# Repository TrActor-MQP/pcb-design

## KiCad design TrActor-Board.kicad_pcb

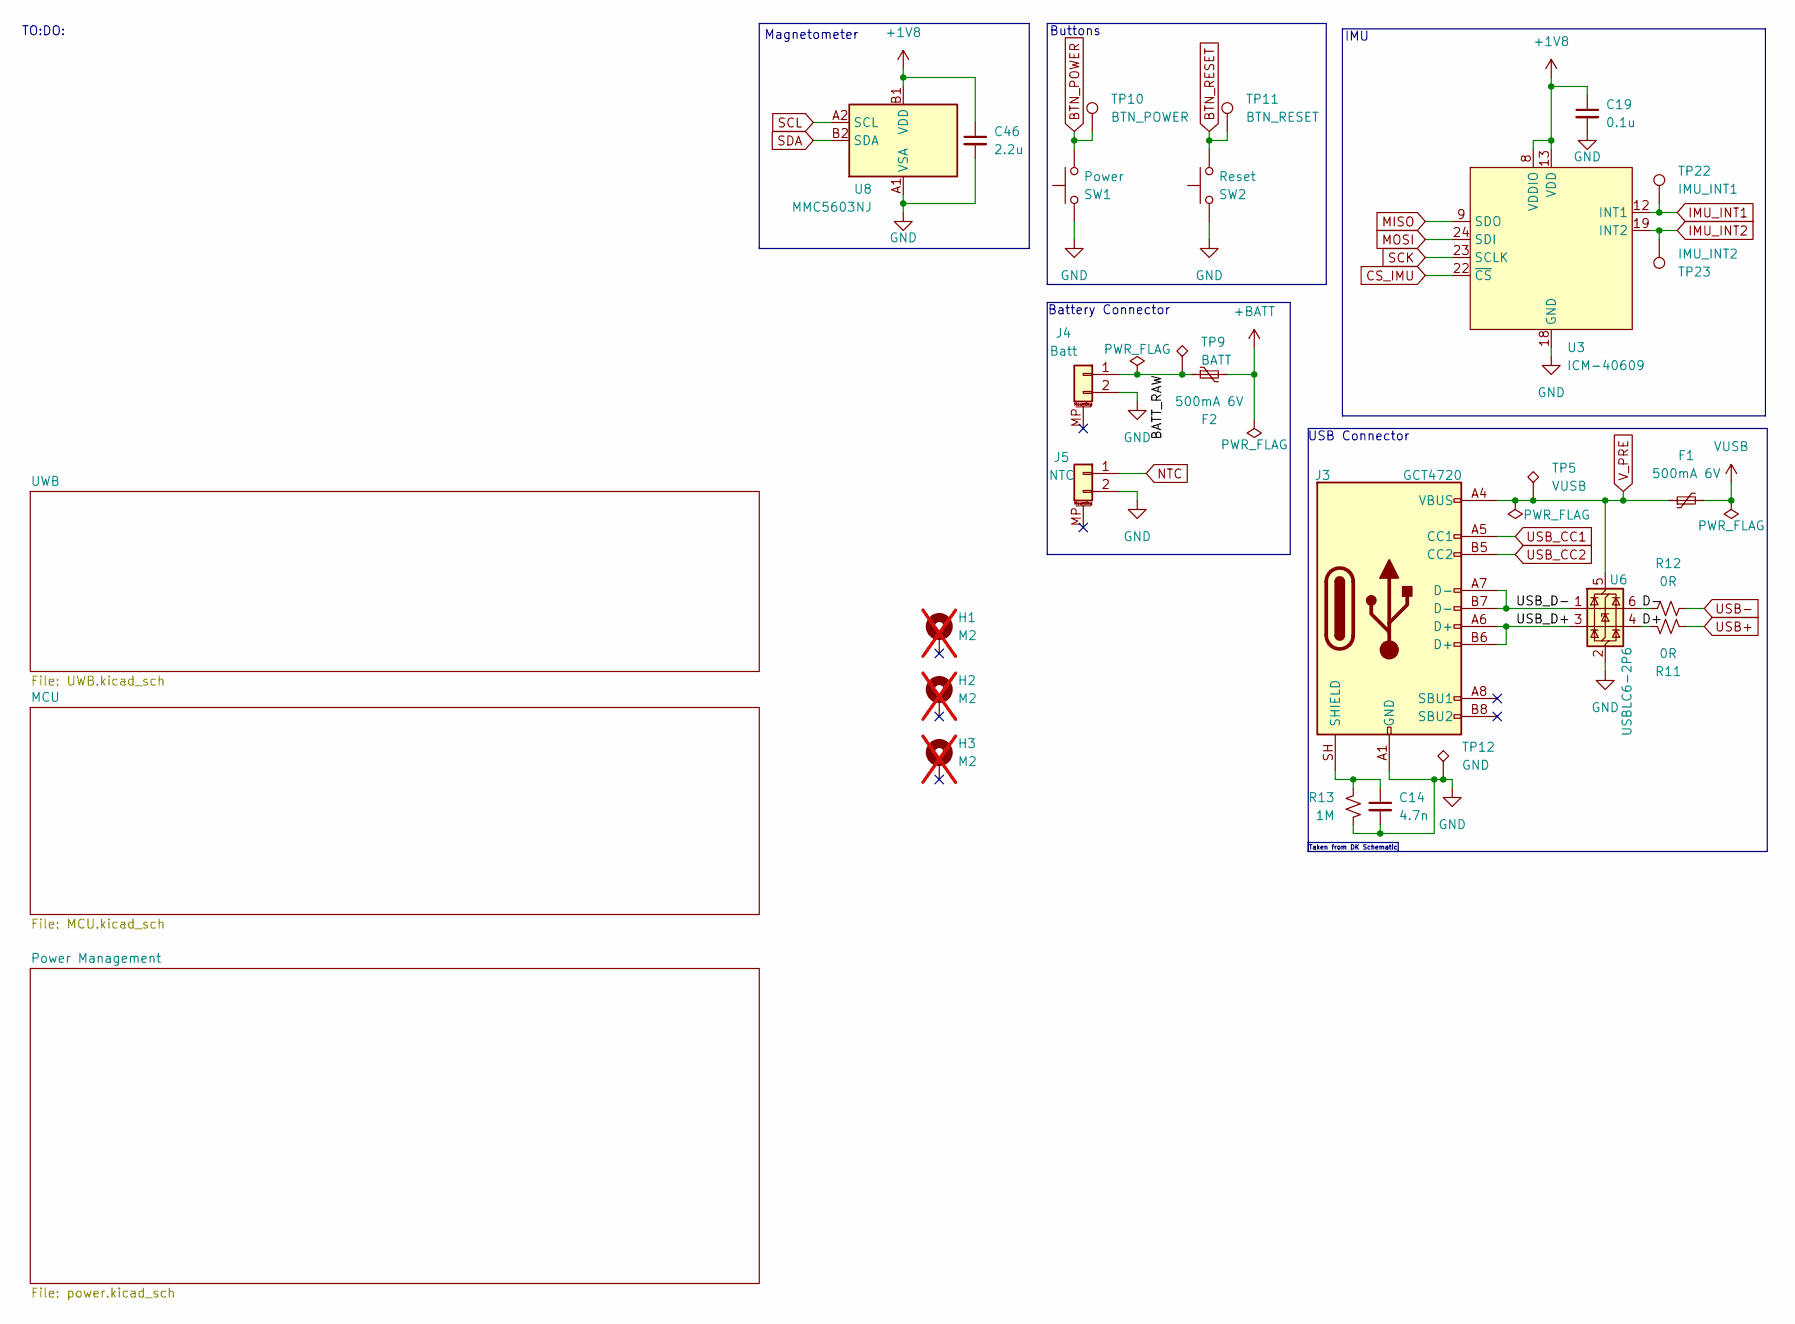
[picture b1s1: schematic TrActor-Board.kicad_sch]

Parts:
C14: 4.7n; C_0402_1005Metric
C19: 0.1u; C_0402_1005Metric
C46: 2.2u; C_0603_1608Metric
F1, F2: 500mA 6V; Fuse_0603_1608Metric
H1, H2, H3: M2; MountingHole_2.2mm_M2_DIN965_Pad_TopBottom; not fitted
J3: GCT4720; GCT_USB4720-03-A_REVA
J4: Batt; JST_PH_S2B-PH-SM4-TB_1x02-1MP_P2.00mm_Horizontal
J5: NTC; JST_SH_SM02B-SRSS-TB_1x02-1MP_P1.00mm_Horizontal
R11, R12: 0R; R_0402_1005Metric
R13: 1M; R_0402_1005Metric
SW1: Power; SW_SPST_EVQP7A
SW2: Reset; SW_SPST_EVQP7A
TP5: VUSB; TestPoint_Pad_1.0x1.0mm
TP9: BATT; TestPoint_Pad_1.0x1.0mm
TP10: BTN_POWER; TestPoint_Pad_D1.0mm
TP11: BTN_RESET; TestPoint_Pad_D1.0mm
TP12: GND; TestPoint_Pad_1.0x1.0mm
TP22: IMU_INT1; TestPoint_Pad_D1.0mm
TP23: IMU_INT2; TestPoint_Pad_D1.0mm
U3: ICM-40609; InvenSense_QFN-24_3x3mm_P0.4mm
U6: USBLC6-2P6; SOT-666
U8: MMC5603NJ; WLP-4_0.86x0.86mm_P0.4mm

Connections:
+1V8: C19.1, C46.1, U3.8 (VDDIO), U3.13 (VDD), U8.B1 (VDD); also elsewhere on the board
+BATT: F2.2; also elsewhere on the board
/BATT_RAW: F2.1, J4.1, TP9.1 (1_1)
/D+: R11.2, U6.4 (I/O2)
/D-: R12.1, U6.6 (I/O1)
/USB_D+: J3.A6 (D+), J3.B6 (D+), U6.3 (I/O2)
/USB_D-: J3.A7 (D-), J3.B7 (D-), U6.1 (I/O1)
BTN_POWER: SW1.1, TP10.1 (1_1); also elsewhere on the board
BTN_RESET: SW2.1, TP11.1 (1_1); also elsewhere on the board
CS_IMU: U3.22 (~CS); also elsewhere on the board
GND: C14.2, C19.2, C46.2, J3.A1 (GND), J3.A12 (GND), J3.B1 (GND), J3.B12 (GND), J4.2, J5.2, R13.2, SW1.2, SW2.2, TP12.1 (1_1), U3.11 (RESV), U3.18 (GND), U3.20 (RESV), U6.2 (GND), U8.A1 (VSA); also elsewhere on the board
IMU_INT1: TP22.1 (1_1), U3.12 (INT1); also elsewhere on the board
IMU_INT2: TP23.1 (1_1), U3.19 (INT2); also elsewhere on the board
MISO: U3.9 (SDO); also elsewhere on the board
MOSI: U3.24 (SDI); also elsewhere on the board
NTC: J5.1; also elsewhere on the board
unnamed: C14.1, J3.SH (SHIELD), R13.1
SCK: U3.23 (SCLK); also elsewhere on the board
SCL: U8.A2 (SCL); also elsewhere on the board
SDA: U8.B2 (SDA); also elsewhere on the board
USB+: R11.1; also elsewhere on the board
USB-: R12.2; also elsewhere on the board
USB_CC1: J3.A5 (CC1); also elsewhere on the board
USB_CC2: J3.B5 (CC2); also elsewhere on the board
VUSB: F1.2; also elsewhere on the board
V_PRE: F1.1, J3.A4 (VBUS), J3.A9 (VBUS), J3.B4 (VBUS), J3.B9 (VBUS), TP5.1 (1_1), U6.5 (VBUS); also elsewhere on the board

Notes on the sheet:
Magnetometer
Taken from DK Schematic
USB Connector
IMU
TO:DO:
Battery Connector
Buttons

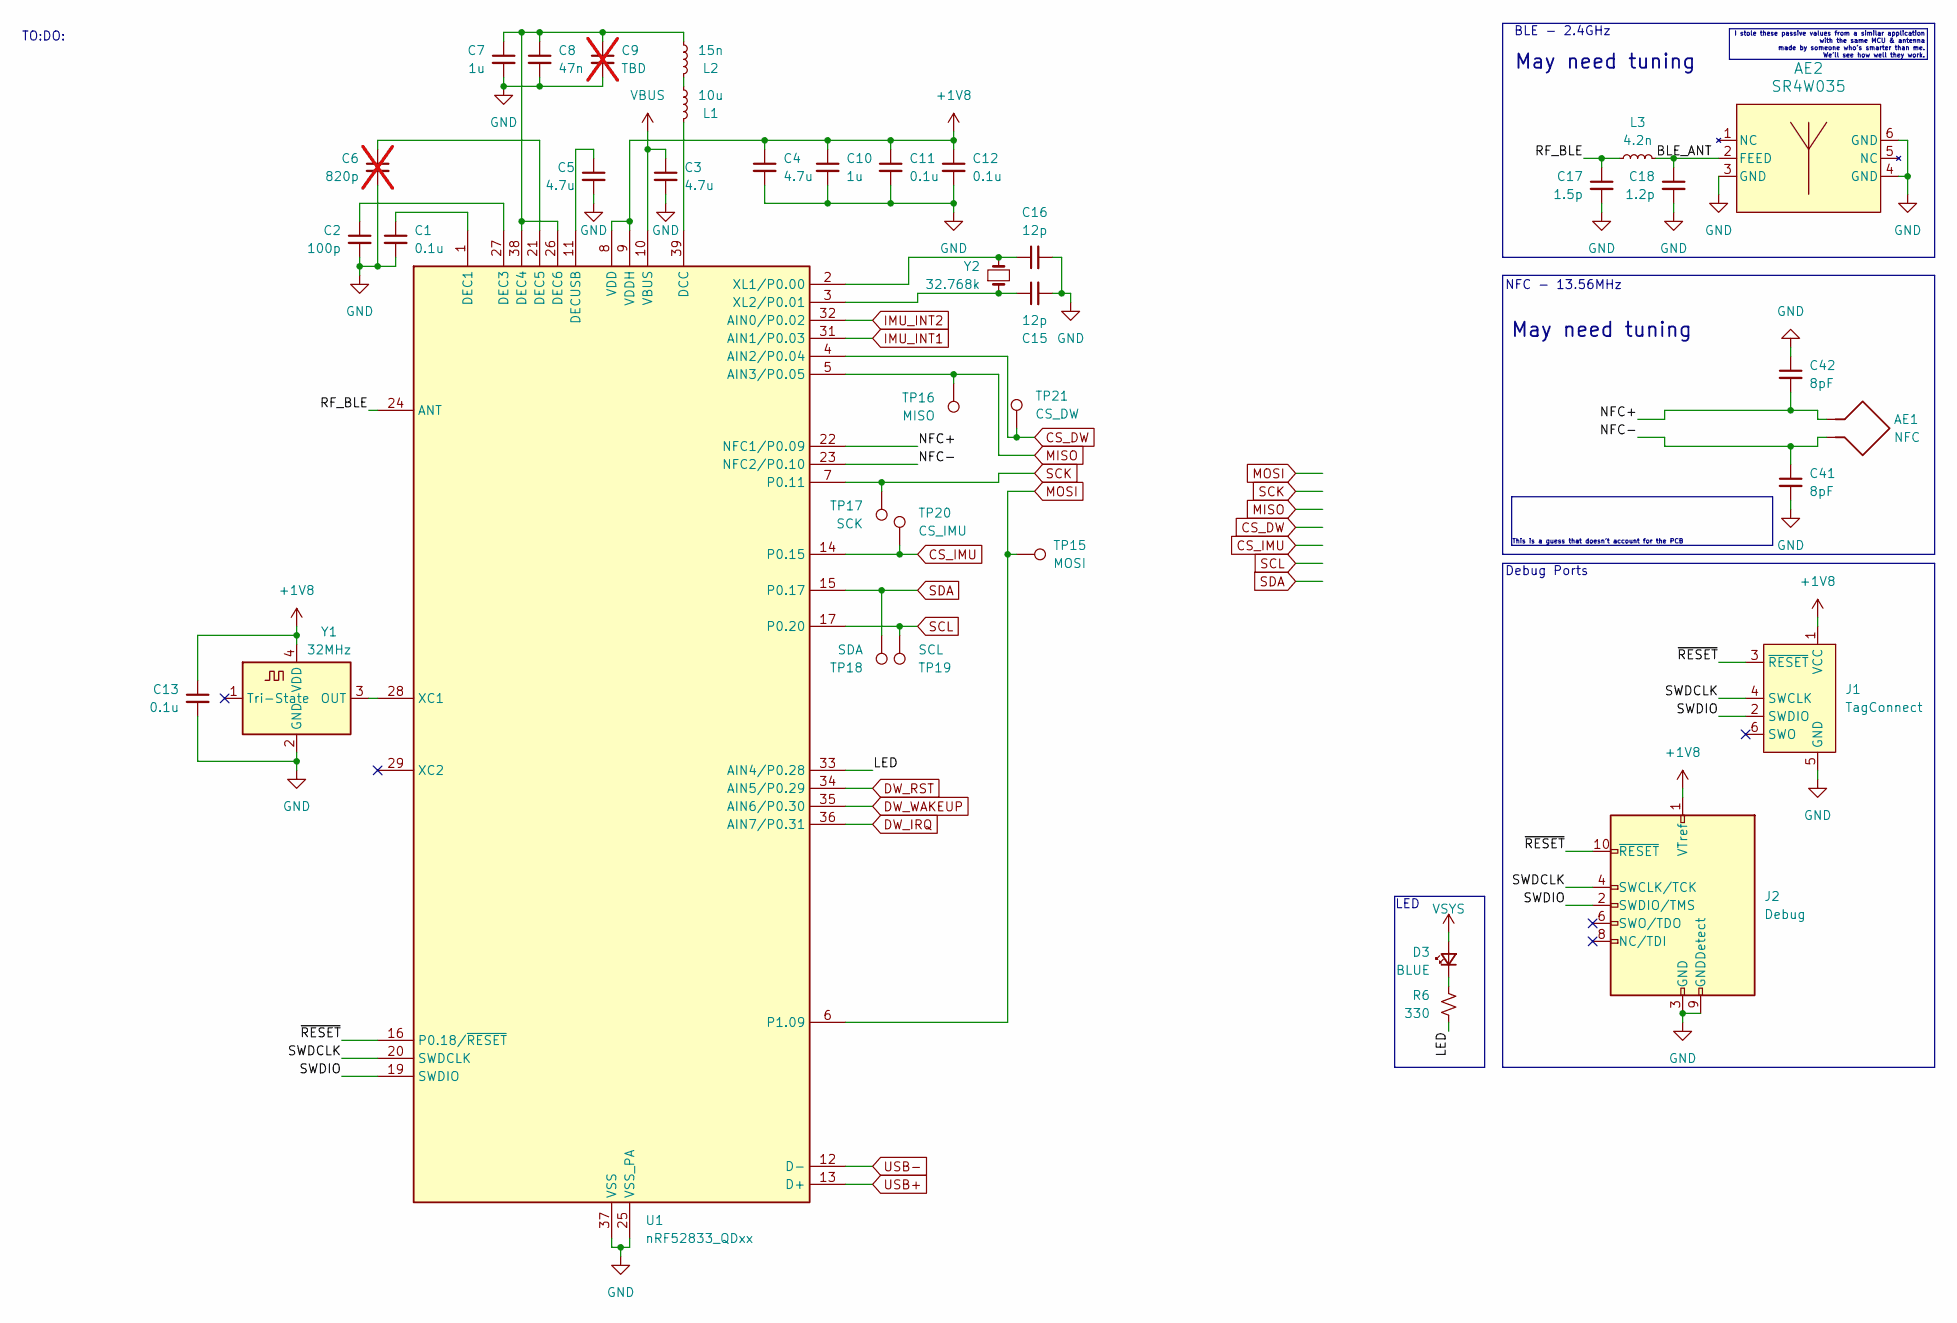
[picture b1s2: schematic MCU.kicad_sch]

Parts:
AE1: NFC; AANI-CH-0029
AE2: SR4W035; SR4W035_4X6_ANT
C1, C11, C12, C13: 0.1u; C_0402_1005Metric
C2: 100p; C_0402_1005Metric
C3, C4, C5: 4.7u; C_0402_1005Metric
C6: 820p; C_0402_1005Metric; not fitted
C7, C10: 1u; C_0402_1005Metric
C8: 47n; C_0402_1005Metric
C9: TBD; C_0402_1005Metric; not fitted
C15, C16: 12p; C_0402_1005Metric
C17: 1.5p; C_0402_1005Metric
C18: 1.2p; C_0402_1005Metric
C41, C42: 8pF; C_0402_1005Metric
D3: BLUE; LED_0603_1608Metric
J1: TagConnect; Tag-Connect_TC2030-IDC-NL_2x03_P1.27mm_Vertical
J2: Debug; PinHeader_2x05_P1.27mm_Vertical
L1: 10u; L_0603_1608Metric
L2: 15n; L_0402_1005Metric
L3: 4.2n; L_0402_1005Metric
R6: 330; R_0402_1005Metric
TP15: MOSI; TestPoint_Pad_D1.0mm
TP16: MISO; TestPoint_Pad_D1.0mm
TP17: SCK; TestPoint_Pad_D1.0mm
TP18: SDA; TestPoint_Pad_D1.0mm
TP19: SCL; TestPoint_Pad_D1.0mm
TP20: CS_IMU; TestPoint_Pad_D1.0mm
TP21: CS_DW; TestPoint_Pad_D1.0mm
U1: nRF52833_QDxx; QFN-40-1EP_5x5mm_P0.4mm_EP3.6x3.6mm
Y1: 32MHz; Oscillator_SMD_ECS_2520MV-xxx-xx-4Pin_2.5x2.0mm
Y2: 32.768k; Crystal_SMD_2012-2Pin_2.0x1.2mm

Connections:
+1V8: C4.1, C10.1, C11.1, C12.1, C13.1, J1.1 (VCC), J2.1 (VTref), U1.8 (VDD), U1.9 (VDDH), U1.18 (VDD), U1.30 (VDD), U1.40 (VDD), Y1.4 (VDD); also elsewhere on the board
/MCU/BLE_ANT: AE2.2 (FEED), C18.1, L3.1
/MCU/LED: R6.2, U1.33 (AIN4/P0.28)
/MCU/NFC+: AE1.1, C42.2, U1.22 (NFC1/P0.09)
/MCU/NFC-: AE1.2, C41.1, U1.23 (NFC2/P0.10)
/MCU/RF_BLE: C17.1, L3.2, U1.24 (ANT)
/MCU/SWDCLK: J1.4 (SWCLK), J2.4 (SWCLK/TCK), U1.20 (SWDCLK)
/MCU/SWDIO: J1.2 (SWDIO), J2.2 (SWDIO/TMS), U1.19 (SWDIO)
/MCU/~RESET: J1.3 (~RESET), J2.10 (~RESET), U1.16 (P0.18/~RESET)
CS_DW: TP21.1 (1_1), U1.4 (AIN2/P0.04); also elsewhere on the board
CS_IMU: TP20.1 (1_1), U1.14 (P0.15); also elsewhere on the board
DW_IRQ: U1.36 (AIN7/P0.31); also elsewhere on the board
DW_RST: U1.34 (AIN5/P0.29); also elsewhere on the board
DW_WAKEUP: U1.35 (AIN6/P0.30); also elsewhere on the board
GND: AE2.3 (GND), AE2.4 (GND), AE2.6 (GND), C1.2, C2.2, C3.2, C4.2, C5.2, C6.2, C7.2, C8.2, C9.2, C10.2, C11.2, C12.2, C13.2, C15.2, C16.2, C17.2, C18.2, C41.2, C42.1, J1.5 (GND), J2.3 (GND), J2.5 (GND), J2.9 (GNDDetect), U1.25 (VSS_PA), U1.37 (VSS), U1.41 (VSS), Y1.2 (GND); also elsewhere on the board
IMU_INT1: U1.31 (AIN1/P0.03); also elsewhere on the board
IMU_INT2: U1.32 (AIN0/P0.02); also elsewhere on the board
MISO: TP16.1 (1_1), U1.5 (AIN3/P0.05); also elsewhere on the board
MOSI: TP15.1 (1_1), U1.6 (P1.09); also elsewhere on the board
unnamed: D3.1 (K), R6.1
unnamed: L1.2, L2.1
unnamed: L1.1, U1.39 (DCC)
unnamed: C1.1, U1.1 (DEC1)
unnamed: C2.1, U1.27 (DEC3)
unnamed: C7.1, C8.1, C9.1, L2.2, U1.26 (DEC6), U1.38 (DEC4)
unnamed: C6.1, U1.21 (DEC5)
unnamed: C5.1, U1.11 (DECUSB)
unnamed: U1.28 (XC1), Y1.3 (OUT)
unnamed: C16.1, U1.2 (XL1/P0.00), Y2.2
unnamed: C15.1, U1.3 (XL2/P0.01), Y2.1
SCK: TP17.1 (1_1), U1.7 (P0.11); also elsewhere on the board
SCL: TP19.1 (1_1), U1.17 (P0.20); also elsewhere on the board
SDA: TP18.1 (1_1), U1.15 (P0.17); also elsewhere on the board
USB+: U1.13 (D+); also elsewhere on the board
USB-: U1.12 (D-); also elsewhere on the board
VBUS: C3.1, U1.10 (VBUS); also elsewhere on the board
VSYS: D3.2 (A); also elsewhere on the board

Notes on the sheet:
May need tuning
This is a guess that doesn't account for the PCB
I stole these passive values from a similar application with the same MCU & antenna made by someone who's smarter than me. We'll see how well they work.
TO:DO:
BLE - 2.4GHz
NFC - 13.56MHz
Debug Ports
LED

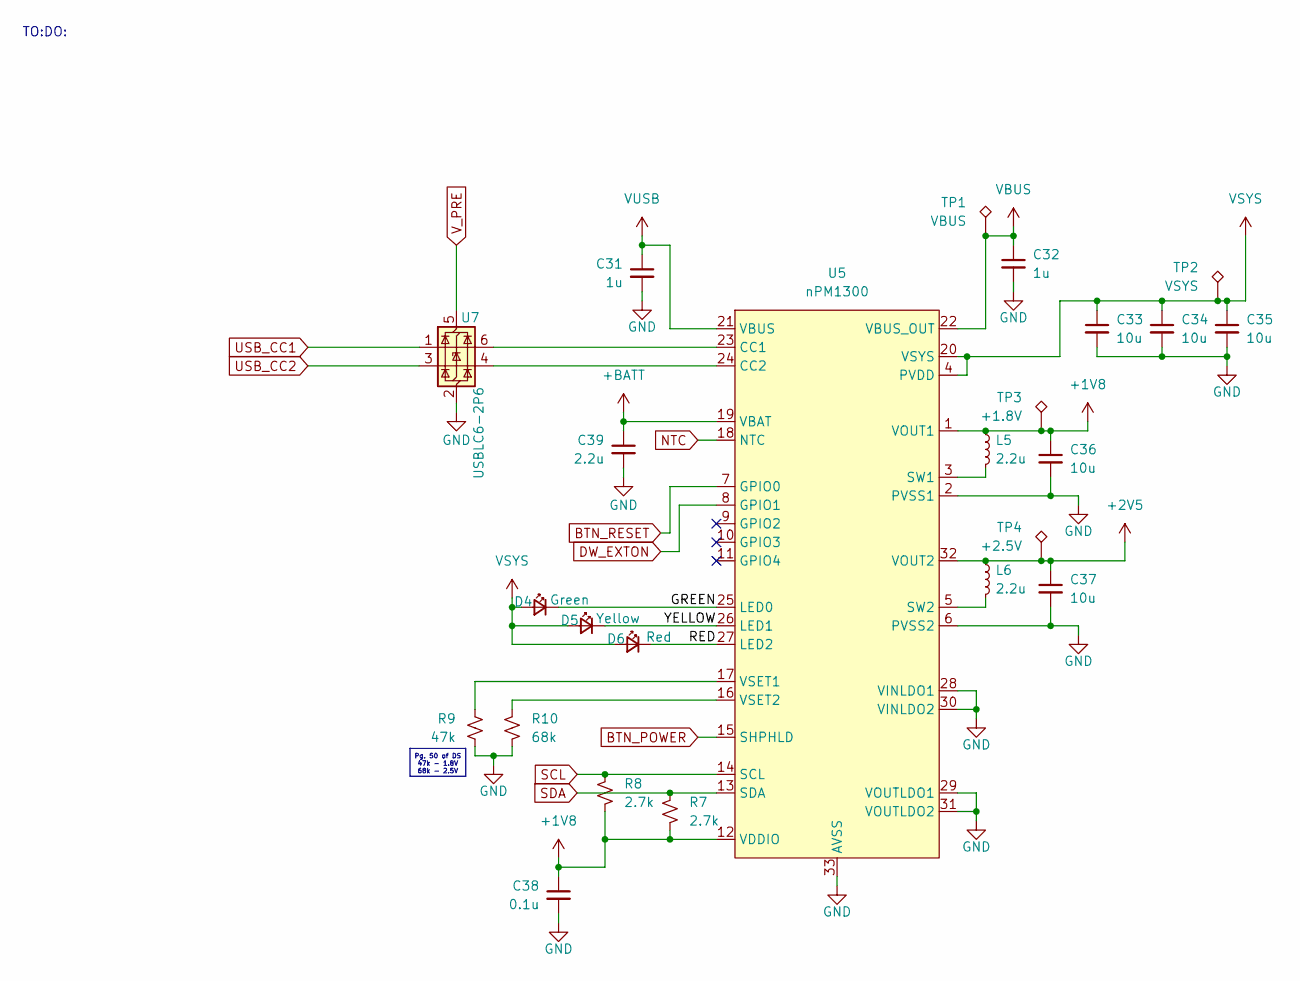
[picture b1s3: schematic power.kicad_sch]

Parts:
C31, C32: 1u; C_0402_1005Metric
C33, C34, C35, C36, C37: 10u; C_0603_1608Metric
C38: 0.1u; C_0402_1005Metric
C39: 2.2u; C_0603_1608Metric
D4: Green; LED_0603_1608Metric
D5: Yellow; LED_0603_1608Metric
D6: Red; LED_0603_1608Metric
L5, L6: 2.2u; L_0805_2012Metric
R7, R8: 2.7k; R_0402_1005Metric
R9: 47k; R_0402_1005Metric
R10: 68k; R_0402_1005Metric
TP1: VBUS; TestPoint_Pad_1.0x1.0mm
TP2: VSYS; TestPoint_Pad_1.0x1.0mm
TP3: +1.8V; TestPoint_Pad_1.0x1.0mm
TP4: +2.5V; TestPoint_Pad_1.0x1.0mm
U5: nPM1300; QFN-32-1EP_5x5mm_P0.5mm_EP3.45x3.45mm_ThermalVias
U7: USBLC6-2P6; SOT-666

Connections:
+1V8: C36.1, C38.1, L5.1, R7.2, R8.2, TP3.1 (1_1), U5.1 (VOUT1), U5.12 (VDDIO); also elsewhere on the board
+2V5: C37.1, L6.1, TP4.1 (1_1), U5.32 (VOUT2); also elsewhere on the board
+BATT: C39.1, U5.19 (VBAT); also elsewhere on the board
/Power Management/GREEN: D4.1 (K), U5.25 (LED0)
/Power Management/RED: D6.1 (K), U5.27 (LED2)
/Power Management/YELLOW: D5.1 (K), U5.26 (LED1)
BTN_POWER: U5.15 (SHPHLD); also elsewhere on the board
BTN_RESET: U5.7 (GPIO0); also elsewhere on the board
DW_EXTON: U5.8 (GPIO1); also elsewhere on the board
GND: C31.2, C32.2, C33.2, C34.2, C35.2, C36.2, C37.2, C38.2, C39.2, R9.2, R10.2, U5.2 (PVSS1), U5.6 (PVSS2), U5.28 (VINLDO1), U5.29 (VOUTLDO1), U5.30 (VINLDO2), U5.31 (VOUTLDO2), U5.33 (AVSS), U7.2 (GND); also elsewhere on the board
NTC: U5.18 (NTC); also elsewhere on the board
unnamed: U5.23 (CC1), U7.6 (I/O1)
unnamed: U5.24 (CC2), U7.4 (I/O2)
unnamed: L5.2, U5.3 (SW1)
unnamed: L6.2, U5.5 (SW2)
unnamed: R9.1, U5.17 (VSET1)
unnamed: R10.1, U5.16 (VSET2)
SCL: R8.1, U5.14 (SCL); also elsewhere on the board
SDA: R7.1, U5.13 (SDA); also elsewhere on the board
USB_CC1: U7.1 (I/O1); also elsewhere on the board
USB_CC2: U7.3 (I/O2); also elsewhere on the board
VBUS: C32.1, TP1.1 (1_1), U5.22 (VBUS_OUT); also elsewhere on the board
VSYS: C33.1, C34.1, C35.1, D4.2 (A), D5.2 (A), D6.2 (A), TP2.1 (1_1), U5.4 (PVDD), U5.20 (VSYS); also elsewhere on the board
VUSB: C31.1, U5.21 (VBUS); also elsewhere on the board
V_PRE: U7.5 (VBUS); also elsewhere on the board

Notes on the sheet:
Pg. 50 of DS 47k - 1.8V 68k - 2.5V
TO:DO:

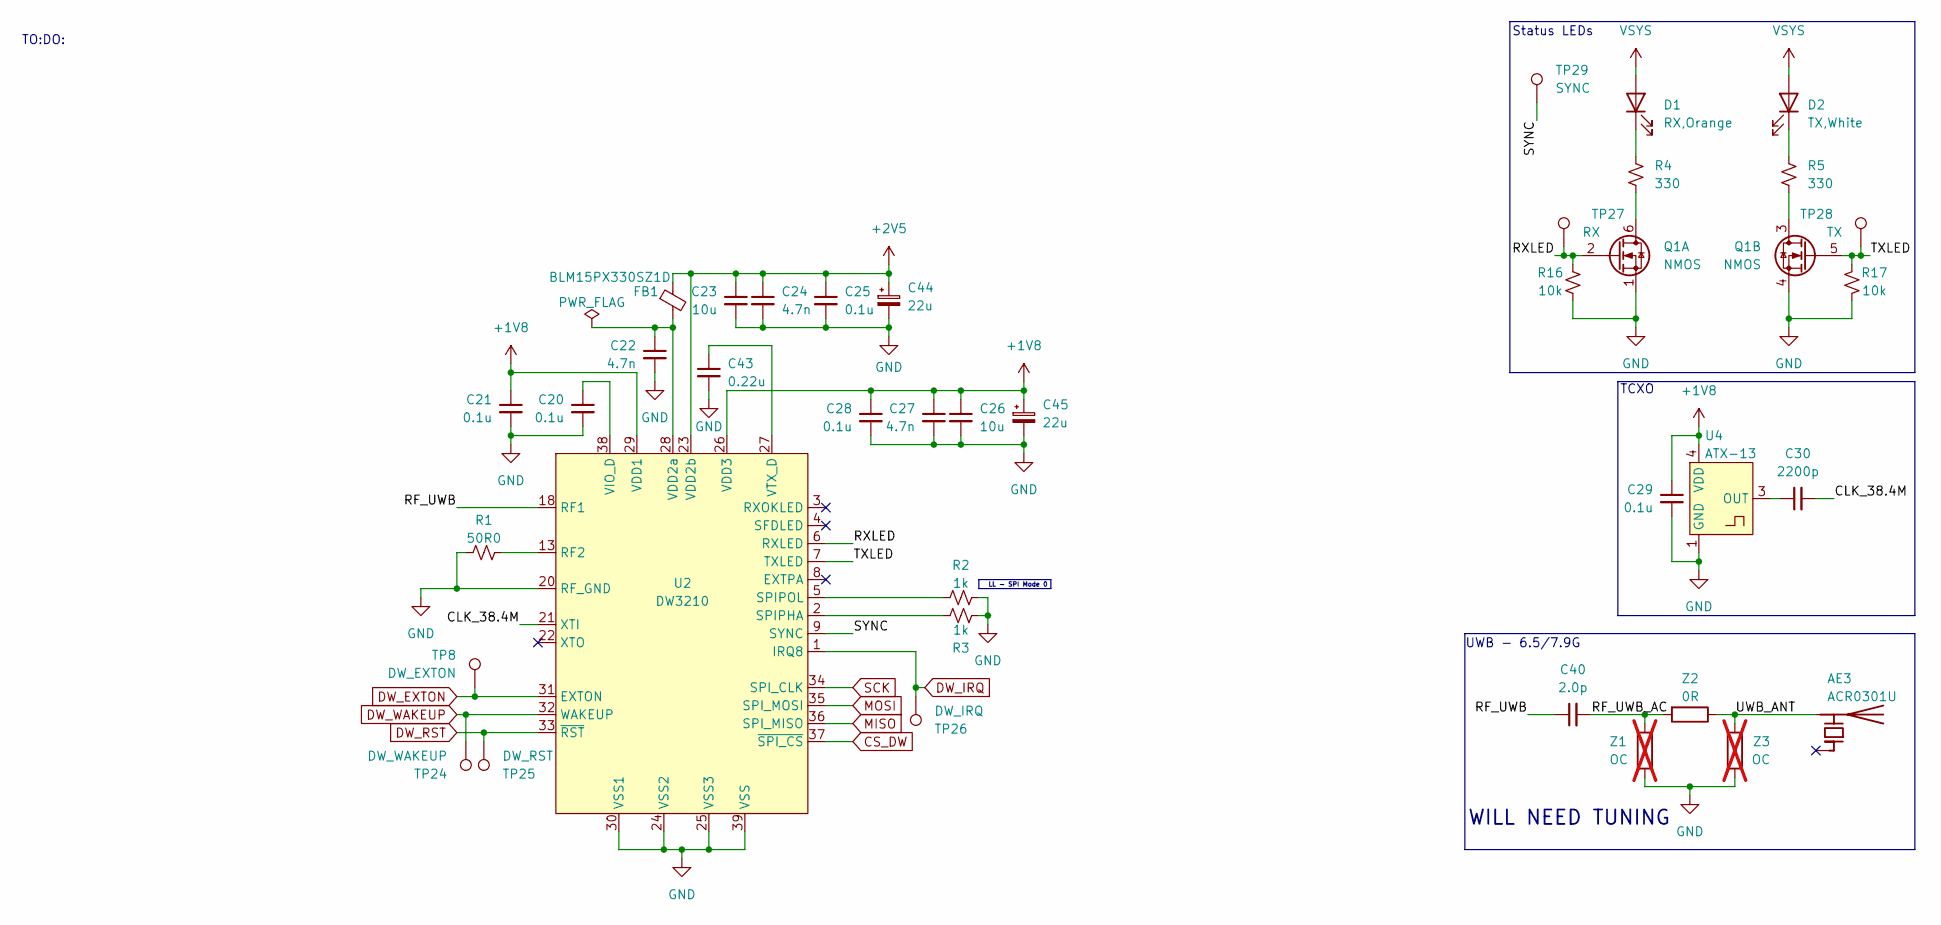
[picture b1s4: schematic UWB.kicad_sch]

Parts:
AE3: ACR0301U
C20, C21, C25, C28, C29: 0.1u; C_0402_1005Metric
C22, C24, C27: 4.7n; C_0402_1005Metric
C23, C26: 10u; C_0603_1608Metric
C30: 2200p; C_0402_1005Metric
C40: 2.0p; C_0402_1005Metric
C43: 0.22u; C_0402_1005Metric
C44, C45: 22u; CP_Elec_4x5.4
D1: RX,Orange; LED_0603_1608Metric
D2: TX,White; LED_0603_1608Metric
FB1: BLM15PX330SZ1D; L_0402_1005Metric
Q1: NMOS; SOT-363_SC-70-6
R1: 50R0; R_0402_1005Metric
R2, R3: 1k; R_0402_1005Metric
R4, R5: 330; R_0402_1005Metric
R16, R17: 10k; R_0402_1005Metric
TP8: DW_EXTON; TestPoint_Pad_D1.0mm
TP24: DW_WAKEUP; TestPoint_Pad_D1.0mm
TP25: DW_RST; TestPoint_Pad_D1.0mm
TP26: DW_IRQ; TestPoint_Pad_D1.0mm
TP27: RX; TestPoint_Pad_D1.0mm
TP28: TX; TestPoint_Pad_D1.0mm
TP29: SYNC; TestPoint_Pad_D1.0mm
U2: DW3210; QFN-40-1EP_5x5mm_P0.4mm
U4: ATX-13; Crystal_SMD_2016-4Pin_2.0x1.6mm
Z1, Z3: OC; L_0402_1005Metric; not fitted
Z2: 0R; L_0402_1005Metric

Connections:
+1V8: C21.1, C26.1, C27.1, C28.1, C29.1, C45.1, U2.26 (VDD3), U2.29 (VDD1), U4.4 (VDD); also elsewhere on the board
+2V5: C23.1, C24.1, C25.1, C44.1, FB1.1, U2.23 (VDD2b); also elsewhere on the board
/UWB/CLK_38.4M: C30.2, U2.21 (XTI)
/UWB/RF_UWB: C40.1, U2.18 (RF1)
/UWB/RF_UWB_AC: C40.2, Z1.1, Z2.2
/UWB/RXLED: Q1.2 (G), R16.2, TP27.1 (1_1), U2.6 (RXLED)
/UWB/SYNC: TP29.1 (1_1), U2.9 (SYNC)
/UWB/TXLED: Q1.5 (G), R17.2, TP28.1 (1_1), U2.7 (TXLED)
/UWB/UWB_ANT: AE3.2 (PCB_Trace_2), Z2.1, Z3.1
CS_DW: U2.37 (~SPI_CS); also elsewhere on the board
DW_EXTON: TP8.1 (1_1), U2.31 (EXTON); also elsewhere on the board
DW_IRQ: TP26.1 (1_1), U2.1 (IRQ8); also elsewhere on the board
DW_RST: TP25.1 (1_1), U2.33 (~RST); also elsewhere on the board
DW_WAKEUP: TP24.1 (1_1), U2.32 (WAKEUP); also elsewhere on the board
GND: C20.2, C21.2, C22.2, C23.2, C24.2, C25.2, C26.2, C27.2, C28.2, C29.2, C43.2, C44.2, C45.2, Q1.1 (S), Q1.4 (S), R1.1, R2.2, R3.1, R16.1, R17.1, U2.10 (RF_GND), U2.11 (RF_GND), U2.12 (RF_GND), U2.14 (RF_GND), U2.15 (RF_GND), U2.16 (RF_GND), U2.17 (RF_GND), U2.19 (RF_GND), U2.20 (RF_GND), U2.24 (VSS2), U2.25 (VSS3), U2.30 (VSS1), U2.39 (VSS), U2.40 (VSS), U4.1 (GND), U4.2 (GND), Z1.2, Z3.2; also elsewhere on the board
MISO: U2.36 (SPI_MISO); also elsewhere on the board
MOSI: U2.35 (SPI_MOSI); also elsewhere on the board
unnamed: D1.1 (K), R4.1
unnamed: D2.1 (K), R5.1
unnamed: Q1.6 (D), R4.2
unnamed: Q1.3 (D), R5.2
unnamed: R1.2, U2.13 (RF2)
unnamed: R3.2, U2.2 (SPIPHA)
unnamed: R2.1, U2.5 (SPIPOL)
unnamed: C22.1, FB1.2, U2.28 (VDD2a)
unnamed: C20.1, U2.38 (VIO_D)
unnamed: C43.1, U2.27 (VTX_D)
unnamed: C30.1, U4.3 (OUT)
SCK: U2.34 (SPI_CLK); also elsewhere on the board
VSYS: D1.2 (A), D2.2 (A); also elsewhere on the board

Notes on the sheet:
UWB - 6.5/7.9G
TCXO
LL - SPI Mode 0
Status LEDs
WILL NEED TUNING
TO:DO:

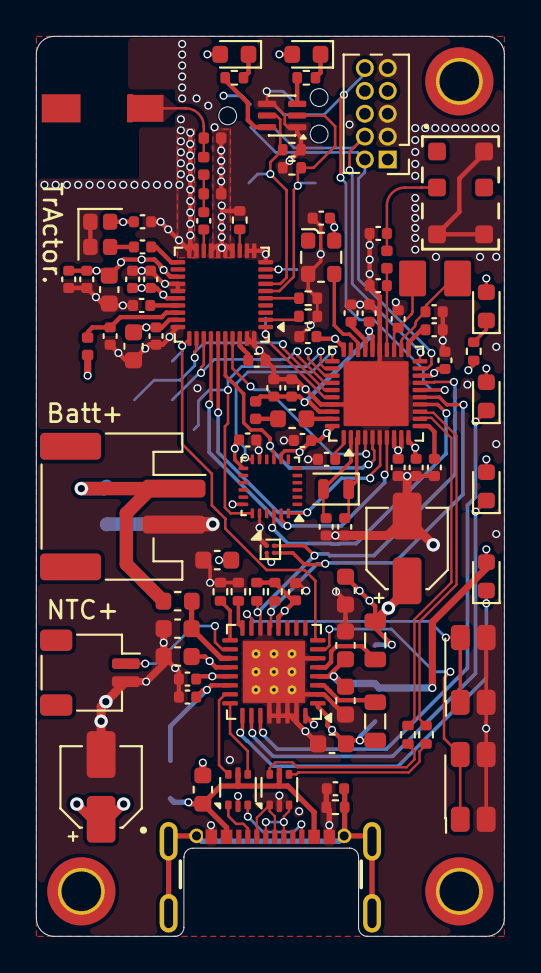
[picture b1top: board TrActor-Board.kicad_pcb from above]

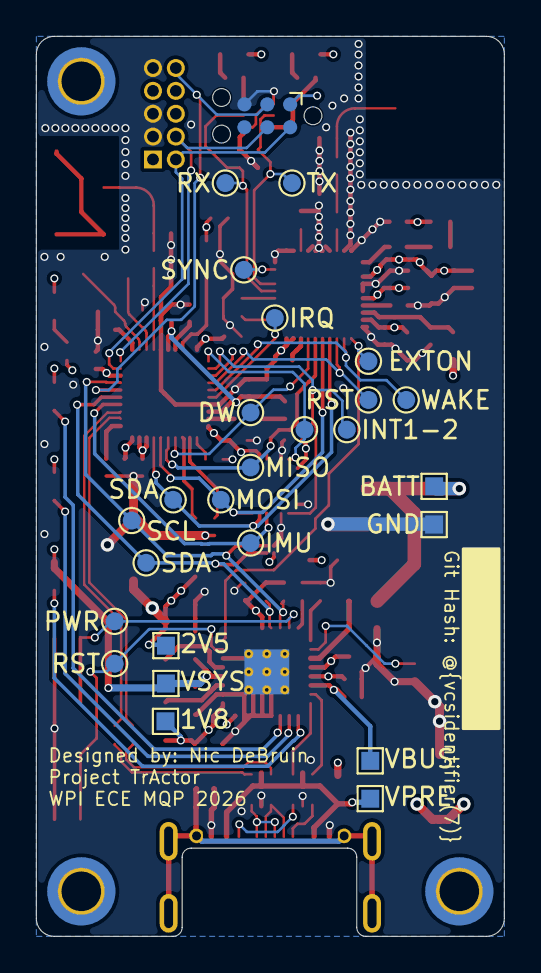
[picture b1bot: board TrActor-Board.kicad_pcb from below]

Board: 6 copper layers, 26.0 x 50.0 mm, 127 parts (26 on the bottom side), 80 nets.
